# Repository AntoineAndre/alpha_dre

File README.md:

# &#945;. Dré

__Or "How to fit an ISO layout in a 40% keyboard ?"__

## Table of contents
- [Presentation](#Presentation)
- [Layout](#Layout)
- [Case](#Case), more details [here](case/case_doc.md)
- [PCB](#PCB), more details [here](pcb/pcb_doc.md)
- [Parts](#Parts)
- [Results](#Results)
- [Renders](#Renders), more details [here](renders/renders_doc.md)

## Presentation

This project started as a need to find a **new mechanical keyboard with a french ISO layout support**. It also aims to keep a minimalist design that we can find on most 40% keyboards. It will therefore include all the 3D CAD files and various pcb related files to conduct the project along with a documentation to build the keyboard.

This keyboard is __Via and Vial compatible__ to give a better user experience (especially when it comes to remapping keys).

__All pictures of this project can be found [here](https://flic.kr/s/aHsmVLZSPn)__ (acrylic case) __and [here](https://flic.kr/s/aHsmVCqc8F)__ (no plate tray mount)

### Layout

The keyboard presents 42 keys that are placed in an ISO layout, and even if the layout seems odd, most of keycaps set will fit this design. With juste 3 layers the keyboard becomes fully usable as shown in the firmware part.

### Case

#### 3D printed version

A top mounted case aimed to be 3D printed has been done to complete the build.

Blueprints are available in dedicated folder, short link to pdf blueprints :
- [global assembly](https://raw.githubusercontent.com/antoineandre/alpha_dre/main/case/3D_print/assembly_blueprint.pdf)
- [top part](https://raw.githubusercontent.com/antoineandre/alpha_dre/main/case/3D_print/bottom_part_blueprint.pdf)
- [bottom part](https://raw.githubusercontent.com/antoineandre/alpha_dre/main/case/3D_print/top_part_blueprint.pdf)

#### Acrylic stack
The case is a *high profile* one (meaning the electronic parts and switches are hidden by the case) and has been designed to be manufactured with only laser cut acrylic plates of various sizes. These plates are fixed with M2 screws (M2x16) and are hidden with rubber bumps on the bottom of the case. This conception leads to a *sandwich mount* keyboard.

In order to give the keyboard a little angle for typing, two different feet have been design to be screwed at the back of the case.

A last option of low profile (barely no case) is available and needs practically no manufacturing. This option leads to a *tray mount* keyboard with no plate (this is the chosen option shown in the beginning of this presentation).

*Side note on the acrylic case : the design was a bit too lose and the gap between keycaps and top layer of the case can be reduced. Furthermore the plate was designed to host plate mounted stabilizers, but the pcb was designed for pcb mounted stabs...*

### PCB

The pcb has been designed with Kicad software and gerbers files are available in the dedicated folder. This pcb hosts an Atmega32U4-AU for the keyboard control and is (as for other electronic components) soldered in surface. 

More on the pcb design available in the documentation file.

### Parts

Here is a global list of all parts needed to perform this keyboard build:

- [ ] Laser cut acrylic plates
- [ ] Screws (M2 for sandwich mount and M3 for skeleton mount)
- [ ] SMD components fot the pcb (see the pcb documentation for more details)
- [ ] pcb plate
- [ ] 42 switches
- [ ] 6.25u and 2u stabilizers
- [ ] ISO keycap set
- [ ] Soldering tools
- [ ] Drill and threading tools

<!-- ## Documents

- [case documentation](case/case_doc.md)
- [pcb documentation](pcb/pcb_doc.md)
- [firmware documentation](firmware/alpha_dre/readme.md) -->

### Results

A first prototype with a simple skeleton case made out of plexiglass have been made to validate that the keyboard was responding correctly to the firmware and was usable. More on the cases will be done in the future (notably with the cut acrylic plates for the sandwich mount and with a 3d printed case).

Second prototype was made with acrylic sandwich plates (as intended in the original project). Two pictures showing the results of this case can be seen below.

### Renders

A bunch of renders have been made to validate the overall looking of the keyboard.

__Complete set of renders__ can be found __[here](docs/renders/renders_doc.md)__

## Aknowledgment

- [Masterzen "Designing a keyboard from scratch" guide](https://www.masterzen.fr/2020/05/03/designing-a-keyboard-part-1/)
- [French mechanical keyboard community](https://github.com/mkbdfr) for their help, feedback and amelioration propositions to make this design as "usable" as possible.

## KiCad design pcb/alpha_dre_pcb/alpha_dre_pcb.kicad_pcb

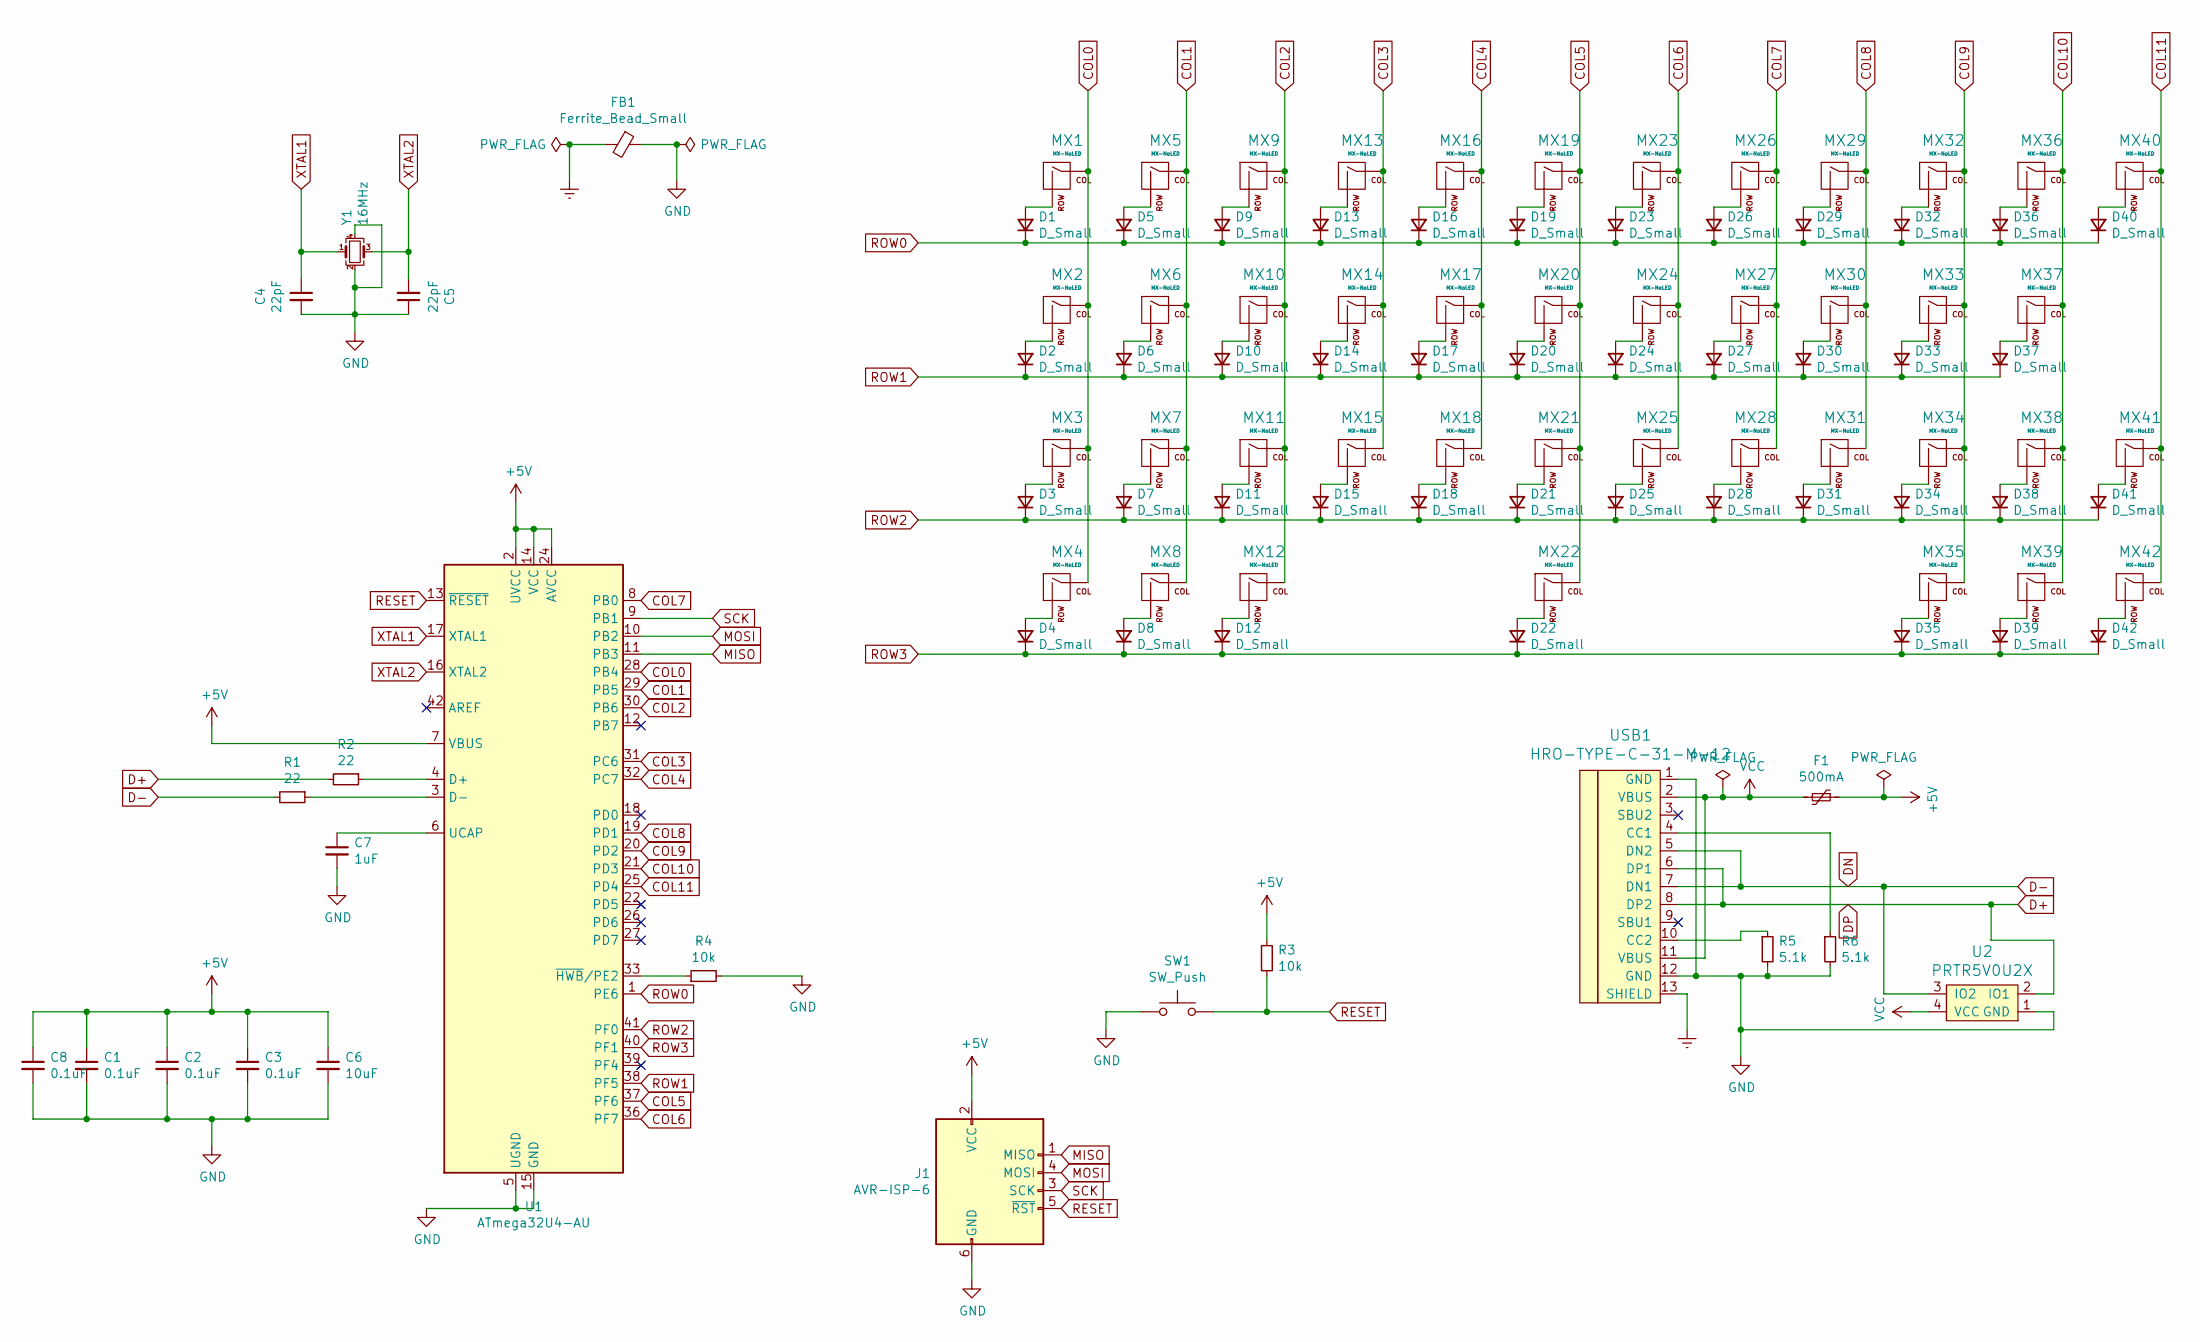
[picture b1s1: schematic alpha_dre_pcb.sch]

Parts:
C1, C2, C3, C8: 0.1uF; C_0805_2012Metric_Pad1.18x1.45mm_HandSolder
C4, C5: 22pF; C_0805_2012Metric_Pad1.18x1.45mm_HandSolder
C6: 10uF; C_0805_2012Metric_Pad1.18x1.45mm_HandSolder
C7: 1uF; C_0805_2012Metric_Pad1.18x1.45mm_HandSolder
D1, D2, D3, D4, D5, D6, D7, D8, D9, D10, D11, D12, D13, D14, D15, D16, D17, D18, D19, D20, D21, D22, D23, D24, D25, D26, D27, D28, D29, D30, D31, D32, D33, D34, D35, D36, D37, D38, D39, D40, D41, D42: D_Small; D_SOD-123-Pretty
F1: 500mA; Fuse_1206_3216Metric_Pad1.42x1.75mm_HandSolder
FB1: Ferrite_Bead_Small; L_0805_2012Metric_Pad1.15x1.40mm_HandSolder
J1: AVR-ISP-6; Reset_Pretty-Mask
MX1, MX3, MX5, MX6, MX7, MX8, MX9, MX10, MX11, MX12, MX13, MX14, MX15, MX16, MX17, MX18, MX19, MX20, MX21, MX23, MX24, MX25, MX26, MX27, MX28, MX29, MX30, MX31, MX32, MX33, MX34, MX35, MX36, MX37, MX38, MX39: MX-NoLED; SW_Cherry_MX_1.00u_PCB_perso
MX2: MX-NoLED; SW_Cherry_MX_1.50u_PCB_perso
MX4, MX42: MX-NoLED; SW_Cherry_MX_1.25u_PCB_perso
MX22: MX-NoLED; MXOnly-6.25U-ReversedStabilizers-NoLED
MX40: MX-NoLED; MXOnly-ISO-ReversedStabilizers-NoLED
MX41: MX-NoLED; SW_Cherry_MX_1.75u_PCB_perso
R1, R2: 22; R_0805_2012Metric_Pad1.20x1.40mm_HandSolder
R3, R4: 10k; R_0805_2012Metric_Pad1.20x1.40mm_HandSolder
R5, R6: 5.1k; R_0805_2012Metric_Pad1.20x1.40mm_HandSolder
SW1: SW_Push; SW_SPST_SKQG_WithStem
U1: ATmega32U4-AU; TQFP-44_10x10mm_P0.8mm
U2: PRTR5V0U2X; SOT143B
USB1: HRO-TYPE-C-31-M-12; HRO-TYPE-C-31-M-12-HandSoldering
Y1: 16MHz; Crystal_SMD_3225-4Pin_3.2x2.5mm_HandSoldering

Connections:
+5V: C1.1, C2.1, C3.1, C6.1, C8.1, F1.1, J1.2 (VCC), R3.1, U1.2 (UVCC), U1.7 (VBUS), U1.14 (VCC), U1.24 (AVCC), U1.34 (VCC), U1.44 (AVCC)
COL0: MX1.1 (COL), MX2.1 (COL), MX3.1 (COL), MX4.1 (COL), U1.28 (PB4)
COL1: MX5.1 (COL), MX6.1 (COL), MX7.1 (COL), MX8.1 (COL), U1.29 (PB5)
COL2: MX9.1 (COL), MX10.1 (COL), MX11.1 (COL), MX12.1 (COL), U1.30 (PB6)
COL3: MX13.1 (COL), MX14.1 (COL), MX15.1 (COL), U1.31 (PC6)
COL4: MX16.1 (COL), MX17.1 (COL), MX18.1 (COL), U1.32 (PC7)
COL5: MX19.1 (COL), MX20.1 (COL), MX21.1 (COL), MX22.1 (COL), U1.37 (PF6)
COL6: MX23.1 (COL), MX24.1 (COL), MX25.1 (COL), U1.36 (PF7)
COL7: MX26.1 (COL), MX27.1 (COL), MX28.1 (COL), U1.8 (PB0)
COL8: MX29.1 (COL), MX30.1 (COL), MX31.1 (COL), U1.19 (PD1)
COL9: MX32.1 (COL), MX33.1 (COL), MX34.1 (COL), MX35.1 (COL), U1.20 (PD2)
COL10: MX36.1 (COL), MX37.1 (COL), MX38.1 (COL), MX39.1 (COL), U1.21 (PD3)
COL11: MX40.1 (COL), MX41.1 (COL), MX42.1 (COL), U1.25 (PD4)
D+: R2.2, U2.2 (IO1), USB1.6 (DP1), USB1.8 (DP2)
D-: R1.2, U2.3 (IO2), USB1.5 (DN2), USB1.7 (DN1)
Earth: FB1.2, USB1.13 (SHIELD)
GND: C1.2, C2.2, C3.2, C4.2, C5.1, C6.2, C7.2, C8.2, FB1.1, J1.6 (GND), R4.2, R5.2, R6.2, SW1.1, U1.5 (UGND), U1.15 (GND), U1.23 (GND), U1.35 (GND), U1.43 (GND), U2.1 (GND), USB1.1 (GND), USB1.12 (GND), Y1.2, Y1.4
MISO: J1.1 (MISO), U1.11 (PB3)
MOSI: J1.4 (MOSI), U1.10 (PB2)
unnamed: C7.1, U1.6 (UCAP)
unnamed: D1.2 (A), MX1.2 (ROW)
unnamed: D2.2 (A), MX2.2 (ROW)
unnamed: D3.2 (A), MX3.2 (ROW)
unnamed: D4.2 (A), MX4.2 (ROW)
unnamed: D5.2 (A), MX5.2 (ROW)
unnamed: D6.2 (A), MX6.2 (ROW)
unnamed: D7.2 (A), MX7.2 (ROW)
unnamed: D8.2 (A), MX8.2 (ROW)
unnamed: D9.2 (A), MX9.2 (ROW)
unnamed: D10.2 (A), MX10.2 (ROW)
unnamed: D11.2 (A), MX11.2 (ROW)
unnamed: D12.2 (A), MX12.2 (ROW)
unnamed: D13.2 (A), MX13.2 (ROW)
unnamed: D14.2 (A), MX14.2 (ROW)
unnamed: D15.2 (A), MX15.2 (ROW)
unnamed: D16.2 (A), MX16.2 (ROW)
unnamed: D17.2 (A), MX17.2 (ROW)
unnamed: D18.2 (A), MX18.2 (ROW)
unnamed: D19.2 (A), MX19.2 (ROW)
unnamed: D20.2 (A), MX20.2 (ROW)
unnamed: D21.2 (A), MX21.2 (ROW)
unnamed: D22.2 (A), MX22.2 (ROW)
unnamed: D23.2 (A), MX23.2 (ROW)
unnamed: D24.2 (A), MX24.2 (ROW)
unnamed: D25.2 (A), MX25.2 (ROW)
unnamed: D26.2 (A), MX26.2 (ROW)
unnamed: D27.2 (A), MX27.2 (ROW)
unnamed: D28.2 (A), MX28.2 (ROW)
unnamed: D29.2 (A), MX29.2 (ROW)
unnamed: D30.2 (A), MX30.2 (ROW)
unnamed: D31.2 (A), MX31.2 (ROW)
unnamed: D32.2 (A), MX32.2 (ROW)
unnamed: D33.2 (A), MX33.2 (ROW)
unnamed: D34.2 (A), MX34.2 (ROW)
unnamed: D35.2 (A), MX35.2 (ROW)
unnamed: D36.2 (A), MX36.2 (ROW)
unnamed: D37.2 (A), MX37.2 (ROW)
unnamed: D38.2 (A), MX38.2 (ROW)
unnamed: D39.2 (A), MX39.2 (ROW)
unnamed: D40.2 (A), MX40.2 (ROW)
unnamed: D41.2 (A), MX41.2 (ROW)
unnamed: D42.2 (A), MX42.2 (ROW)
unnamed: R1.1, U1.3 (D-)
unnamed: R2.1, U1.4 (D+)
unnamed: R4.1, U1.33 (~HWB~/PE2)
unnamed: R5.1, USB1.10 (CC2)
unnamed: R6.1, USB1.4 (CC1)
RESET: J1.5 (~RST), R3.2, SW1.2, U1.13 (~RESET)
ROW0: D1.1 (K), D5.1 (K), D9.1 (K), D13.1 (K), D16.1 (K), D19.1 (K), D23.1 (K), D26.1 (K), D29.1 (K), D32.1 (K), D36.1 (K), D40.1 (K), U1.1 (PE6)
ROW1: D2.1 (K), D6.1 (K), D10.1 (K), D14.1 (K), D17.1 (K), D20.1 (K), D24.1 (K), D27.1 (K), D30.1 (K), D33.1 (K), D37.1 (K), U1.38 (PF5)
ROW2: D3.1 (K), D7.1 (K), D11.1 (K), D15.1 (K), D18.1 (K), D21.1 (K), D25.1 (K), D28.1 (K), D31.1 (K), D34.1 (K), D38.1 (K), D41.1 (K), U1.41 (PF0)
ROW3: D4.1 (K), D8.1 (K), D12.1 (K), D22.1 (K), D35.1 (K), D39.1 (K), D42.1 (K), U1.40 (PF1)
SCK: J1.3 (SCK), U1.9 (PB1)
VCC: F1.2, U2.4 (VCC), USB1.2 (VBUS), USB1.11 (VBUS)
XTAL1: C4.1, U1.17 (XTAL1), Y1.1
XTAL2: C5.2, U1.16 (XTAL2), Y1.3

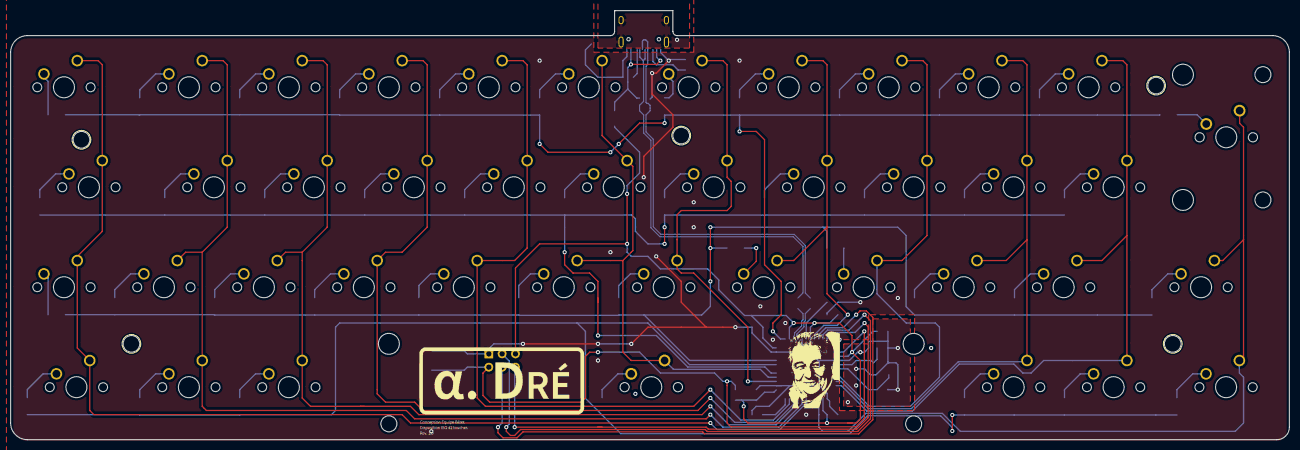
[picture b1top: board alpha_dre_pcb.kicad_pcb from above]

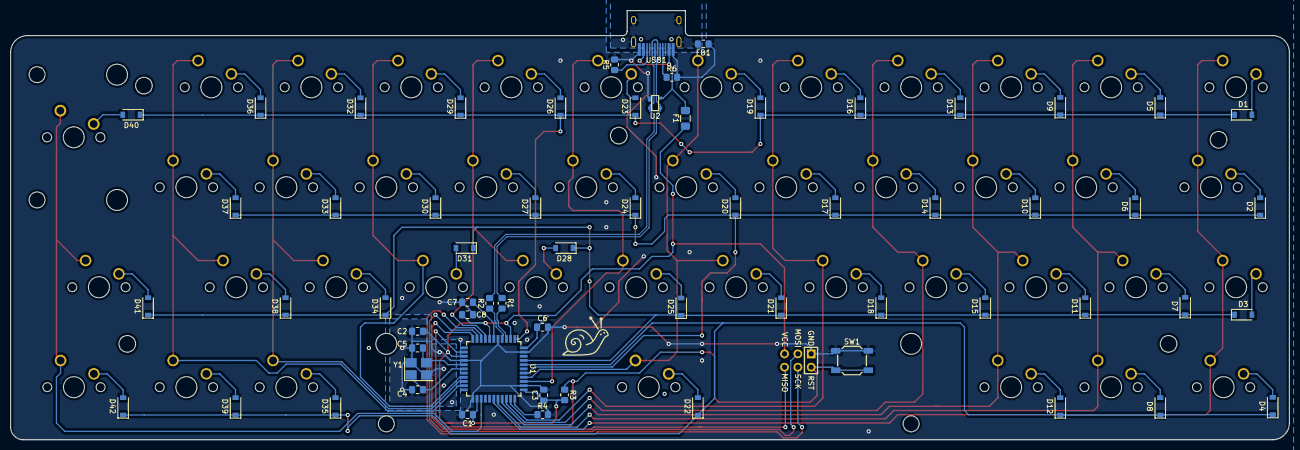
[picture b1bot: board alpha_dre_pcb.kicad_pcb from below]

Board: 2 copper layers, 243.7 x 81.8 mm, 109 parts (65 on the bottom side), 76 nets.

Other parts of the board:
Ref**: Val**; escargot_design
Ref**#2: Val**; info_design
Ref**#3: Val**; alpha_dre_design

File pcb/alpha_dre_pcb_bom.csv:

Id;Designator;Package;Quantity;Designation;Soldered ?
11;FB1;L_0805_2012Metric_Pad1.15x1.40mm_HandSolder;1;Ferrite_Bead_Small;
12;USB1;HRO-TYPE-C-31-M-12-HandSoldering;1;HRO-TYPE-C-31-M-12;
13;U2;SOT143B;1;PRTR5V0U2X;
14;SW1;SW_SPST_SKQG_WithStem;1;SW_Push;
15;R6,R5;R_0805_2012Metric_Pad1.20x1.40mm_HandSolder;2;5.1k;
16;R4,R3;R_0805_2012Metric_Pad1.20x1.40mm_HandSolder;2;10k;
17;R2,R1;R_0805_2012Metric_Pad1.20x1.40mm_HandSolder;2;22;
18;J1;Reset_Pretty-Mask;1;AVR-ISP-6;
19;C8,C3,C2,C1;C_0805_2012Metric_Pad1.18x1.45mm_HandSolder;4;0.1uF;
20;Y1;Crystal_SMD_3225-4Pin_3.2x2.5mm_HandSoldering;1;16MHz;
21;U1;TQFP-44_10x10mm_P0.8mm;1;ATmega32U4-AU;
22;F1;Fuse_1206_3216Metric_Pad1.42x1.75mm_HandSolder;1;500mA;
23;C7;C_0805_2012Metric_Pad1.18x1.45mm_HandSolder;1;1uF;
24;C6;C_0805_2012Metric_Pad1.18x1.45mm_HandSolder;1;10uF;
25;C5,C4;C_0805_2012Metric_Pad1.18x1.45mm_HandSolder;2;22pF;
26;D42,D41,D40,D39,D38,D37,D36,D35,D34,D33,D32,D31,D30,D29,D28,D27,D26,D25,D24,D23,D22,D21,D20,D19,D18,D17,D16,D15,D14,D13,D12,D11,D10,D9,D8,D7,D6,D5,D4,D3,D2,D1;D_SOD-123-Pretty;42;D_Small;

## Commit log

2021-04-16 Initial commit
    Migration from gitlab to github.
    Private repo at the moment
    Rename the project Alpha Dré
2021-04-16 Add gerbers
    Add gerbers to manufacture the PCB
    Add aknowlegment to the readme file
2021-04-17 Update renders
    Add holes for the tray mounted version (update gerbers)
    Add new rends with precise dimensions
2021-04-17 Add readme file for case conception
2021-04-17 Added gerbers and renders
2021-04-17 Add build status in readme
2021-04-18 Add trechnical drawings for case fabrication
    Add snail drawing for PCB
2021-04-18 Add alpha dre ai design for pcb
2021-04-18 Add information design for PCB
2021-04-18 Update case files, pcb drawings
2021-04-18 Final changes before ordering acrylic plates
2021-04-18 Clean kicad project
2021-04-18 Change pcb color to dark
2021-04-18 Clean renders, update readme to go public
2021-04-18 Update renders, go public
2021-04-18 Update readme and add renders
2021-04-23 Update renders and readme
2021-05-10 Add BOM for soldering
2021-05-13 Update multiple readme to present prototype results
    Change the render folder to move it in the docs folder
    Add the firmware folder with the .hex files to flash the keyboard and work on the keymaps
    Add the pictures made with the prototype
2021-05-13 Update readme to correct a miss link
2021-05-13 Remove script from embbed flickr images
2021-05-15 Update Readme and firmware
    Readme slight update with more markdown
    Firmware update to host the media control on the Fun2 layer
2021-05-15 Update pic to remove embed from flickr
2021-05-15 Change license to GPL3
2021-05-15 typo corection for render .md link
2021-05-26 Add Via + Vial compat
    Change a bit the outline of the readme to give more space to the practical information and put the nice pictures and renders at the end of the document.
    Update Readme with last set of pictures made on the acrylic case.
    Add Via + Vial compat
    TBD info.json in firmware folder
2021-05-27 Add info.json to firmware
    Remove .elf and .map from precompiled hex firmware
2021-06-06 Rework one the case
    Rev 2 case with tighter space between caps and case
    Start the conception of 3D printed case (integrated)
2021-06-29 Add 3D printed case version and clean folders for concerning the case
2021-06-29 update readme and docs
2021-06-29 update rendering file
2021-06-29 Update Readme and docs with new renders and more details
